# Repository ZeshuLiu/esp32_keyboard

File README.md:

# 使用esp32为控制器的机械键盘

## **JOKER60**
`Joker 60` 
### **简介**
Joker60是一把poker配列61键键盘，具有一个fn键和一个pn键。
fn键用于输入第二层的键值，如<kbd>F1</kbd>、<kbd>ESC</kbd>（当左上角键被设置为<kbd>`</kbd>时）\
\
OLED屏幕可以显示当前模式，fn键状态。并且具有每30分钟提醒休息的功能，也可以自己修改源代码进行配置\
具有外接电池位置(PCB上B+、GND) 、外接LED灯或其他部件位置(x_LED)和i2c总线接口（*OLED屏幕使用中、可以串联其他不同地址的i2c设备同时使用*）

## **JOKER60 v2**
`Joker60 v2` 
### **简介**
外形与Joker60完全一致，大部分零件均通用。\
Joker60换用了ch9329芯片，可以支持媒体键（音量增加、减小等）。\
电路板进行了大面积敷铜，使用Kicad进行绘制，工程文件在Joker60_v2文件夹内。\
电路部分经过重新设计可以支持常驻型的usb拓展模块（详见Joker60_v2\usb_ext）并且可以板载电池。\
大小写指示灯更换了位置。

## **MASTER YODA**
`Master Yoda` 
### **简介**
一个小的键盘，可以用来打游戏等。

---
## **如何使用**
## **所需工具**
1. **电烙铁及焊锡等** ***必须***\
    推荐使用可调温电烙铁，普通电烙铁也可以。尽量选择头部比较尖锐的烙铁，方便焊接小零件。*有些元件非常小，因此建议先学习电烙铁使用方法，不要一上来就焊接*
2. **螺丝刀** ***必须***\
    一把3.5mm十字花螺丝刀足够
3. **万用表** ***可选***\
    推荐购买一个万用表，可以方便得检查焊接是否正确。没有也不影响正常组装，但是一旦出现问题难以排查。*万用表质量不需要非常好，便宜的就能够胜任*
4. **镊子** ***可选但是强烈推荐***\
    部分零件非常小，除非你的手特别灵活或者你特别闲脾气又好否则没有镊子你会气死。
5. **小刀** ***可选***\
    用来修整3D打印带来的毛边等。小号的壁纸刀最好。
6. **电线** ***v1.0版本必须***\
    用来飞线。建议使用26AWG粗细的。
7. **BOM表上的其他零件** ***必须***\
    [JOKER60 BOM](https://github.com/LiuZSChina/esp32_keyboard/blob/main/Joker60/01/BOM_PCB_Joker60_ver1_2022-04-18.csv)。除了芯片类的东西比如螺丝、二极管等尽量多买几个，*不建议买正好数量，尤其是螺丝*。建议在立创商城搜索相关零件，如果去淘宝购买注意要购买针脚一样的（***USB接口和开关是重点***）否则装不上。（当然我是在淘宝买的，比较便宜 **:D**

---
###  **PCB部分**
Gerber文件：
1. [JOKER60 PCB](https://github.com/LiuZSChina/esp32_keyboard/blob/main/Joker60/01/Gerber_PCB_Joker60_ver1.zip) 
2. [JOKER60_v2 PCB](https://github.com/LiuZSChina/esp32_keyboard/blob/main/Joker60_v2/Joker60_v2_gerber/Joker60_v2_gerber_1026.zip) \
大部分PCB定制厂商都支持直接使用Gerber文件制作。推荐制作1.6mm厚度。
### **外壳、定位板部分**
外壳、定位板文件：
1. [JOKER60 外壳](https://github.com/LiuZSChina/esp32_keyboard/tree/main/Joker60/3D/ver1.0)\
-定位板推荐使用1.5mm厚度。不锈钢、亚克力等都可以，但是手感不同。样机使用不锈钢、1.5mm激光切割\
-外壳为stl文件、可以直接进行3D打印。打印后压入热熔螺母（M3、外径4.3mm，长度4mm）（需要使用电烙铁进行操作）\
-（可选）亚克力推荐使用2.5mm左右材料进行制造，装饰面板需要与屏幕盖板粘合。不使用这些（亚克力材质的）零件不影响使用，但是电路板会暴露在外，容易积灰。
### **制作**
1. 找厂家生产pcb和外壳等，并购买所需要元件（详见BOM表）
2. 按照BOM表上的元件位号焊接材料，主要二极管（1N4147）有反正之分，请注意区分。
3. 刷入固件，详见各版本介绍中烧录条目。源码中的库需要在Arduino中安装。
### **烧录**
+ **1.0版本**\
    需要将开关打至接通ch340的档位，具体方向和焊接方向有关，可以从电脑设备管理器中查看是否连接上ch340进行判断(***v1.0版本（Gerber_PCB_Joker60_ver1）* 中ch340的tx和rx接线是反的，需要飞线调整，并且用小刀割断pcb上的连线**)\
    将gnd和boot短接后通电(**MasterYoda上采用了按键的形式**)，进入下载模式，使用arduino ide或其他编辑器上传固件（具体方法网上很多教程）。gnd和boot在断开的情况再次断电再通电即可退出下载模式运行键盘程序，此时usb口功能通过开关选择ch340和ch9328在串口调试和USB键盘之间切换，*无法同时使用*

### **快捷键**
+ 开启、关闭内置LED灯：<kbd>Pn</kbd> + <kbd>L</kbd>
+ 重置倒计时：<kbd>Pn</kbd> + <kbd>C</kbd>
+ 连接模式转换：<kbd>Pn</kbd> + <kbd>M</kbd> 并且保持三秒以上

### **2.0版本**
——2022.11——\
修复了大部分问题。\
可以开机切换模式。\
**已知问题：** 
1. 暂无

### **2.1版本**——未发布
*预计更改*：
1. 增加CapsLock指示
2. 蓝牙可以常时连接，可以快速切换在连接的蓝牙设备进行输入或者在连接到usb设备上输入

---
## 历史版本
### **1.0版本**
——2022.4——\
初始发布版本，具有蓝牙和有线连接两种方式。\
**已知问题：** 
1. USB转蓝牙模式会导致死机
2. 更改模式需要重新烧录代码
3. CH340N的rx、tx接反了，需要飞线连接。

## ~~JOKER40~~ **(未完成)**

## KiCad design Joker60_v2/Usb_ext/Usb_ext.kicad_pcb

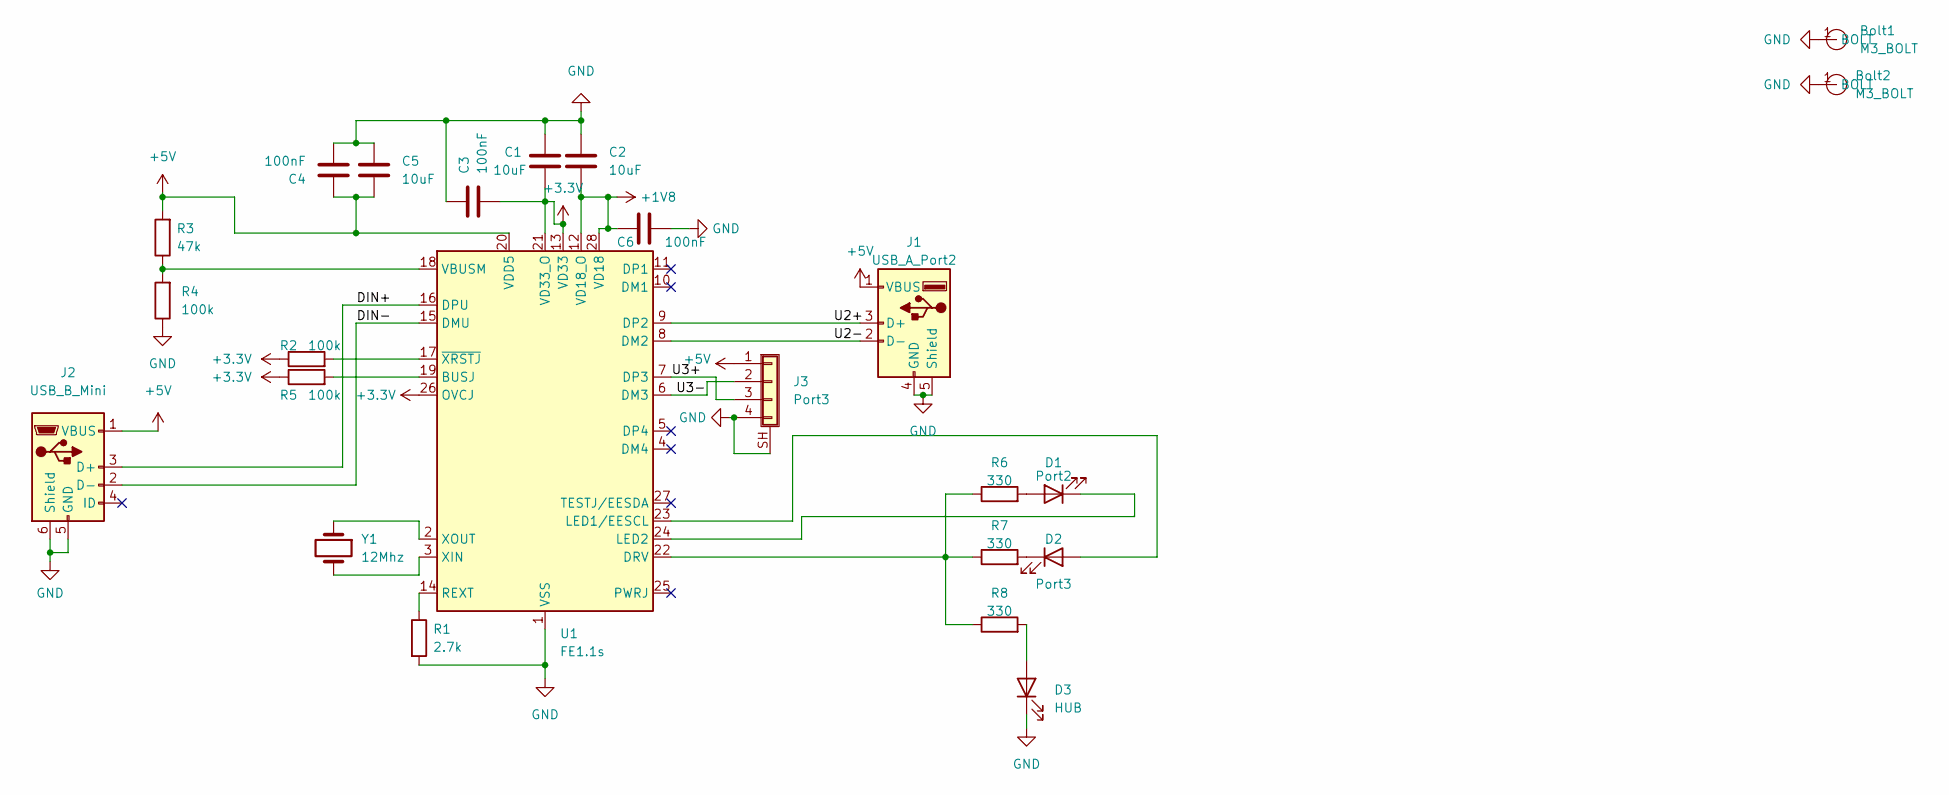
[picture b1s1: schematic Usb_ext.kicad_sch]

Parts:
Bolt1, Bolt2: M3_BOLT; M3 BOLT
C1, C2, C5: 10uF; C_0805_2012Metric_Pad1.18x1.45mm_HandSolder
C3, C4, C6: 100nF; C_0805_2012Metric_Pad1.18x1.45mm_HandSolder
D1: Port2; LED_0805_2012Metric_Pad1.15x1.40mm_HandSolder
D2: Port3; LED_0805_2012Metric_Pad1.15x1.40mm_HandSolder
D3: HUB; LED_0805_2012Metric_Pad1.15x1.40mm_HandSolder
J1: USB_A_Port2; USB_A_Molex_67643_Horizontal
J2: USB_B_Mini; USB_Micro-B_Wuerth_629105150521_CircularHoles
J3: Port3; JST_PH_S4B-PH-SM4-TB_1x04-1MP_P2.00mm_Horizontal
R1: 2.7k; R_0805_2012Metric_Pad1.20x1.40mm_HandSolder
R2, R4, R5: 100k; R_0805_2012Metric_Pad1.20x1.40mm_HandSolder
R3: 47k; R_0805_2012Metric_Pad1.20x1.40mm_HandSolder
R6, R7, R8: 330; R_0805_2012Metric_Pad1.20x1.40mm_HandSolder
U1: FE1.1s; SSOP-28_3.9x9.9mm_P0.635mm
Y1: 12Mhz; Crystal_SMD_HC49-SD_HandSoldering

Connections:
+1V8: C2.2, C6.1, U1.12 (VD18_O), U1.28 (VD18)
+3.3V: C1.2, C3.2, R2.1, R5.1, U1.13 (VD33), U1.21 (VD33_O), U1.26 (OVCJ)
+5V: C4.1, C5.2, J1.1 (VBUS), J2.1 (VBUS), J3.1, R3.2, U1.20 (VDD5)
/DIN+: J2.3 (D+), U1.16 (DPU)
/DIN-: J2.2 (D-), U1.15 (DMU)
/U2+: J1.3 (D+), U1.9 (DP2)
/U2-: J1.2 (D-), U1.8 (DM2)
/U3+: J3.3, U1.7 (DP3)
/U3-: J3.2, U1.6 (DM3)
GND: Bolt1.1 (BOLT), Bolt2.1 (BOLT), C1.1, C2.1, C3.1, C4.2, C5.1, C6.2, D3.1 (K), J1.4 (GND), J1.5 (Shield), J2.5 (GND), J2.6 (Shield), J3.4, J3.SH (Shield), R1.2, R4.1, U1.1 (VSS)
unnamed: D1.1 (K), U1.24 (LED2)
unnamed: D1.2 (A), R6.2
unnamed: D2.1 (K), R7.2
unnamed: D2.2 (A), U1.23 (LED1/EESCL)
unnamed: D3.2 (A), R8.2
unnamed: R1.1, U1.14 (REXT)
unnamed: R2.2, U1.17 (~XRSTJ)
unnamed: R3.1, R4.2, U1.18 (VBUSM)
unnamed: R5.2, U1.19 (BUSJ)
unnamed: R6.1, R7.1, R8.1, U1.22 (DRV)
unnamed: U1.2 (XOUT), Y1.1
unnamed: U1.3 (XIN), Y1.2

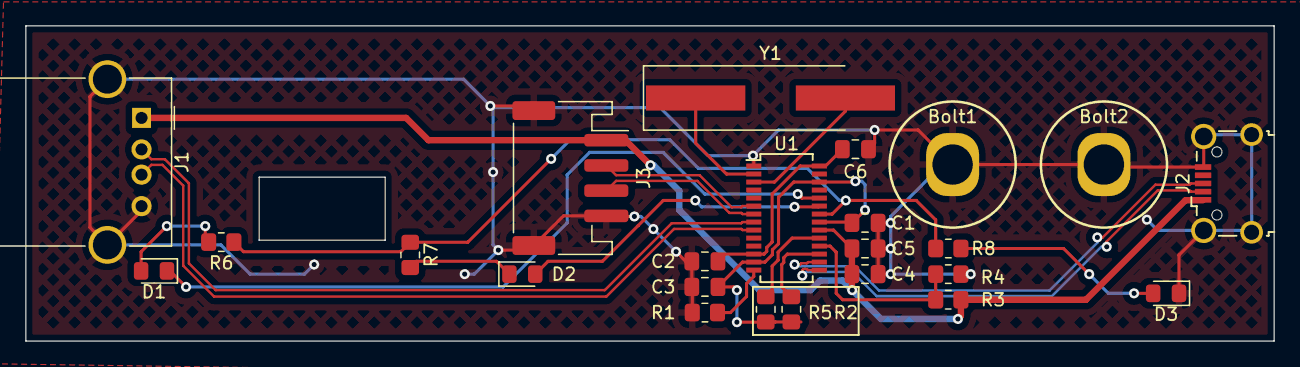
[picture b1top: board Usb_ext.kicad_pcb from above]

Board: 2 copper layers, 99.0 x 25.0 mm, 24 parts (0 on the bottom side), 22 nets.

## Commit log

2022-03-28 init1
2022-03-30 ble dbg
2022-04-04 go_on
2022-04-06 Half Worked
    Left half of the keyboard works fine!
    Right remains to be finished!
2022-04-16 40&60
2022-04-26 V0,1
2022-04-26 Ready to release
2022-04-28 New Layout "Joker Layout"
    Joker Layout is good!
    But need learning to get famillar
2022-06-10 Speed up
2022-06-20 MasterYoda support！
2022-06-20 Ignore
2022-07-28 New model--Master Yoda
    An 18-key pad for gaming &numbers typing!
2022-07-28 Create LICENSE
2022-08-10 Filter refined&Fn Bug fixed
    Increased filtering step from 3to5, reduced the possibility of giving multi input.
    When quitting Fn-layer, unlike previous version, every key will be released.
2022-08-17 bugfix
2022-09-06 noting changed
2022-10-17 Filtering Upgrade&Display Fixed
    Now you can have the correct displaying on your device !
    And FAKE responding reduced Greatly!
    Jimmy 20221017
2022-10-17 jign
2022-10-17 not important
2022-11-19 media code
2022-11-19 New Model Joker60_v2
